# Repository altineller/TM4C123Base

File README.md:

# TM4C123Base

## Reference Design using TM4C123GH6PM suitable for small robotics

This is a MCU board for using the ARM Cortex-M4 TM4C123GH6PM microcontroller in small robotics.

It is the same MCU as the TI TM4C123 Launchpad: http://www.ti.com/tool/EK-TM4C123GXL , except for all the pins are available, and the hibernate circuit works. It also has a backup battery enabling the RTC functions, hibernate and wake-up operations. It can turn on or off an external power supply.

The reason we developed this board is that the TM4C123GXL board does not fit well in small robots, and one can not take advantage of the hibernate functionality.

It can be programmed by using CCS, gcc-arm, or Energia, and it is thoroughly tested. To program it, you either need a TM4C123GXL board or an external debug probe like XDS110.

Although 402 size smd components are used, it is relatively easy to solder it with hand using a hot air station. The gerbers are produced so any board house can build them.

This board has been extensively tested, and also powers the robotics project at https://github.com/altineller/DuckiePilot

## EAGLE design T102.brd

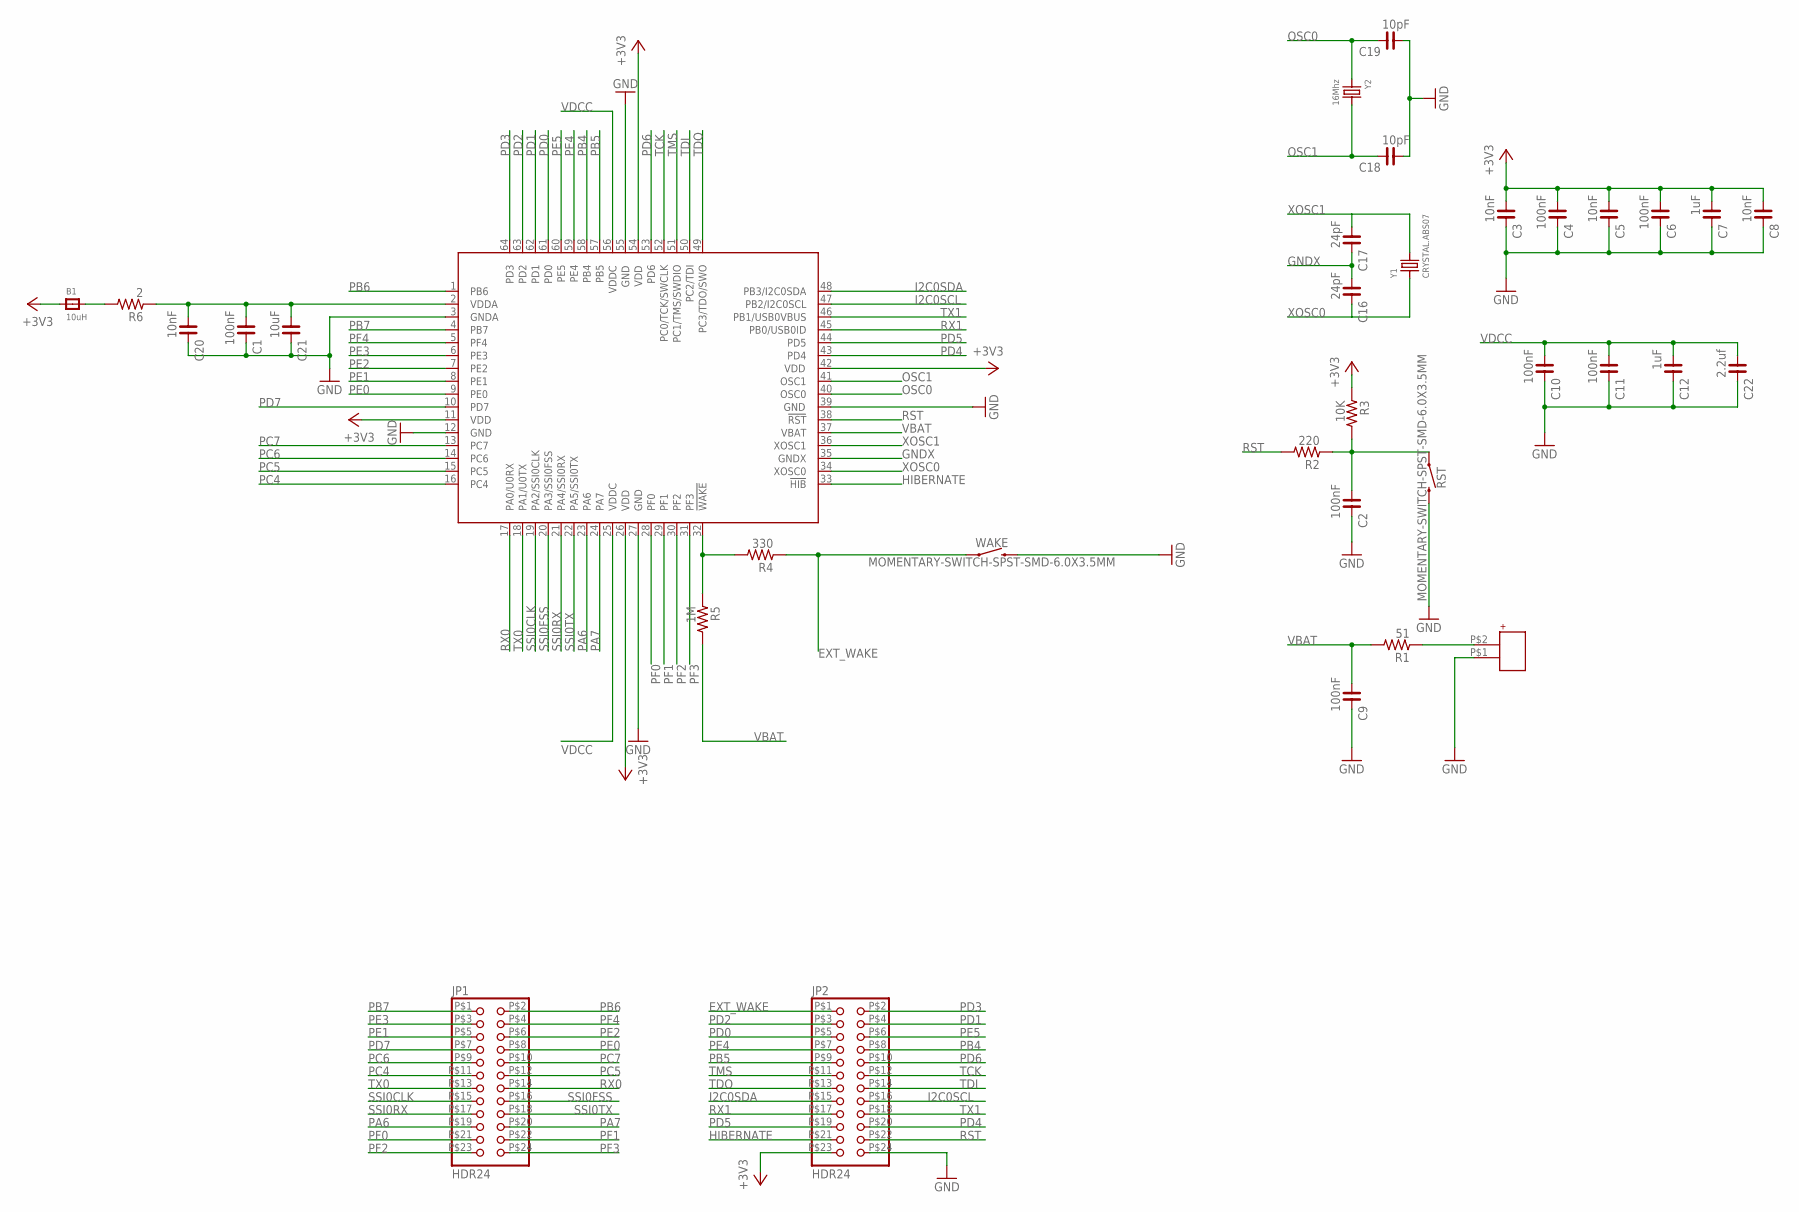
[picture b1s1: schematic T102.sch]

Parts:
B1: 10uH; _0603
C1, C2, C4, C6, C9, C10, C11: 100nF; C0402
C3, C5, C8, C20: 10nF; C0402
C7, C12: 1uF; C0402
C16, C17: 24pF; C0402
C18, C19: 10pF; C0402
C21: 10uF; C0603
C22: 2.2uf; C0603
IC1: TM4C123[7,G]XXPM; PM_S-PQFP-G64
JP1, JP2: HDR24
R1: 51; R0402
R2: 220; R0402
R3: 10K; R0402
R4: 330; R0402
R5: 1M; R0402
R6: 2; R0402
RST: MOMENTARY-SWITCH-SPST-SMD-6.0X3.5MM; TACTILE_SWITCH_SMD_6.0X3.5MM
U$1: JST-MICROBAT
WAKE: MOMENTARY-SWITCH-SPST-SMD-6.0X3.5MM; TACTILE_SWITCH_SMD_6.0X3.5MM
Y1: CRYSTAL.ABS07; ABS07
Y2: 16Mhz; 6X3.3MM

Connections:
+3V3: B1.1, C3.1, C4.1, C5.1, C6.1, C7.1, C8.1, IC1.11 (VDD), IC1.26 (VDD), IC1.42 (VDD), IC1.54 (VDD), JP2.P$23 (23), R3.1
EXT_WAKE: JP2.P$1 (1), R4.1, WAKE.1
GND: C1.2, C2.2, C3.2, C4.2, C5.2, C6.2, C7.2, C8.2, C9.2, C10.2, C11.2, C12.2, C18.1, C19.1, C20.2, C21.2, C22.2, IC1.3 (GNDA), IC1.12 (GND), IC1.27 (GND), IC1.39 (GND), IC1.55 (GND), JP2.P$24 (24), RST.2, U$1.P$1, WAKE.2
GNDX: C16.1, C17.2, IC1.35 (GNDX)
HIBERNATE: IC1.33 (!HIB), JP2.P$21 (21)
I2C0SCL: IC1.47 (PB2/I2C0SCL), JP2.P$16 (16)
I2C0SDA: IC1.48 (PB3/I2C0SDA), JP2.P$15 (15)
unnamed: R1.1, U$1.P$2
unnamed: C2.1, R2.1, R3.2, RST.1
unnamed: C1.1, C20.1, C21.1, IC1.2 (VDDA), R6.1
unnamed: B1.2, R6.2
N_WAKE: IC1.32 (!WAKE), R4.2, R5.1
OSC0: C19.2, IC1.40 (OSC0), Y2.1
OSC1: C18.2, IC1.41 (OSC1), Y2.2
PA6: IC1.23 (PA6), JP1.P$19 (19)
PA7: IC1.24 (PA7), JP1.P$20 (20)
PB4: IC1.58 (PB4), JP2.P$8 (8)
PB5: IC1.57 (PB5), JP2.P$9 (9)
PB6: IC1.1 (PB6), JP1.P$2 (2)
PB7: IC1.4 (PB7), JP1.P$1 (1)
PC4: IC1.16 (PC4), JP1.P$11 (11)
PC5: IC1.15 (PC5), JP1.P$12 (12)
PC6: IC1.14 (PC6), JP1.P$9 (9)
PC7: IC1.13 (PC7), JP1.P$10 (10)
PD0: IC1.61 (PD0), JP2.P$5 (5)
PD1: IC1.62 (PD1), JP2.P$4 (4)
PD2: IC1.63 (PD2), JP2.P$3 (3)
PD3: IC1.64 (PD3), JP2.P$2 (2)
PD4: IC1.43 (PD4), JP2.P$20 (20)
PD5: IC1.44 (PD5), JP2.P$19 (19)
PD6: IC1.53 (PD6), JP2.P$10 (10)
PD7: IC1.10 (PD7), JP1.P$7 (7)
PE0: IC1.9 (PE0), JP1.P$8 (8)
PE1: IC1.8 (PE1), JP1.P$5 (5)
PE2: IC1.7 (PE2), JP1.P$6 (6)
PE3: IC1.6 (PE3), JP1.P$3 (3)
PE4: IC1.59 (PE4), JP2.P$7 (7)
PE5: IC1.60 (PE5), JP2.P$6 (6)
PF0: IC1.28 (PF0), JP1.P$21 (21)
PF1: IC1.29 (PF1), JP1.P$22 (22)
PF2: IC1.30 (PF2), JP1.P$23 (23)
PF3: IC1.31 (PF3), JP1.P$24 (24)
PF4: IC1.5 (PF4), JP1.P$4 (4)
RST: IC1.38 (!RST), JP2.P$22 (22), R2.2
RX0: IC1.17 (PA0/U0RX), JP1.P$14 (14)
RX1: IC1.45 (PB0/USB0ID), JP2.P$17 (17)
SSI0CLK: IC1.19 (PA2/SSI0CLK), JP1.P$15 (15)
SSI0FSS: IC1.20 (PA3/SSI0FSS), JP1.P$16 (16)
SSI0RX: IC1.21 (PA4/SSI0RX), JP1.P$17 (17)
SSI0TX: IC1.22 (PA5/SSI0TX), JP1.P$18 (18)
TCK: IC1.52 (PC0/TCK/SWCLK), JP2.P$12 (12)
TDI: IC1.50 (PC2/TDI), JP2.P$14 (14)
TDO: IC1.49 (PC3/TDO/SWO), JP2.P$13 (13)
TMS: IC1.51 (PC1/TMS/SWDIO), JP2.P$11 (11)
TX0: IC1.18 (PA1/U0TX), JP1.P$13 (13)
TX1: IC1.46 (PB1/USB0VBUS), JP2.P$18 (18)
VBAT: C9.1, IC1.37 (VBAT), R1.2, R5.2
VDCC: C10.1, C11.1, C12.1, C22.1, IC1.25 (VDDC), IC1.56 (VDDC)
XOSC0: C16.2, IC1.34 (XOSC0), Y1.1
XOSC1: C17.1, IC1.36 (XOSC1), Y1.2

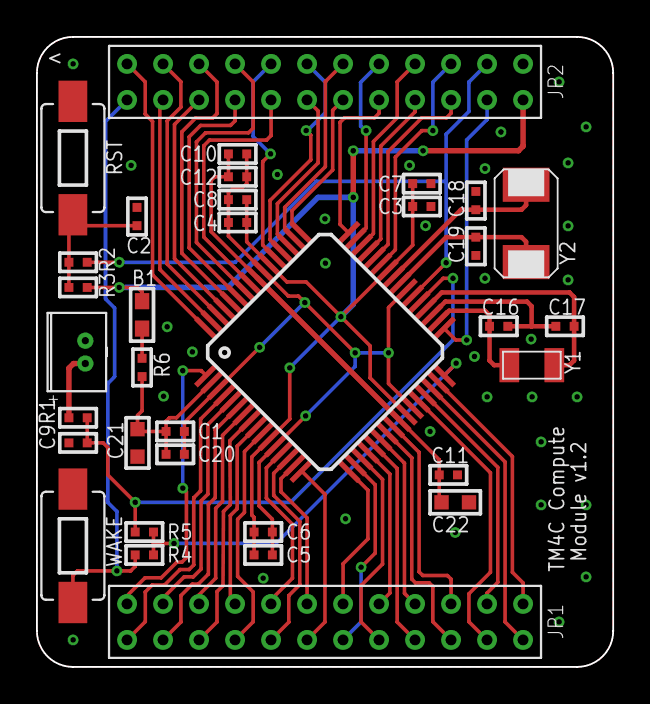
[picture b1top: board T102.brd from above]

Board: 2 copper layers, 32.0 x 35.0 mm, 34 parts (0 on the bottom side), 60 nets.

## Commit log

2019-02-15 first commit
    added the brd and the sch
2019-02-15 added gerber files
2019-10-10 new version

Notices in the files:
parts and their libraries:
rc-master-smd: Copyright (C) 2007, Bob Starr
microbuilder: This work is placed in the public domain, and may be freely used for commercial and non-commercial work with the following conditions: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
